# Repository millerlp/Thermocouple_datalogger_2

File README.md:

## Thermocouple_datalogger_2
### Luke Miller 2017

This repository contains code to run a 8-channel thermocouple
datalogger based on Arduino-type hardware. Currently there are 2 revisions,
A and B, which differ in the type of thermocouple-to-digital chip they use.
Revision A uses the older MAX31855K chip, while Revision B uses the more
recent MAX31856 that effectively superseded the MAX31855 series. Revision A
isn't recommended for new builds. 

The directory `TempTracker` contains the primary files used to run a 
datalogger board, while the `testing` directory contains various utilities
used to test the basic functions of a datalogger board or to help calibrate
a board. 

## Required libraries:
* https://github.com/millerlp/TClib2
* https://github.com/millerlp/Adafruit_MAX31856 - fork of the original Adafruit_MAX31856 library, mainly changed to return NAN temperature values automatically if there is an error. 
* https://github.com/millerlp/RTClib - to run the onboard real time clock chip DS3231M
* https://github.com/greiman/SdFat - for reading/writing SD cards
* https://github.com/greiman/SSD1306Ascii - for writing to OLED displays

## Hardware designs

Eagle `.sch` and `.brd` design files are provided in the `Eagle_files` directory, along
with images of the designs. 

## Parts list

See the file `Thermocouple_datalogger_parts.xlsx` in the `Parts` directory for a 
list of all of the chips and other parts needed to build a board. There are 
separate sheets for Revision A and B, be careful to use the appropriate sheet. The 
majority of the parts should be available from a single vendor such as Digikey.com,
but the OLED display screens and thermocouple connectors need to be sourced 
elsewhere. 

For the OLED displays, any 128x64 pixel I2C SSD1306-based board should 
work (typically 0.96" size). These are available from several vendors on sites like
Amazon or Ebay. Be aware that there are I2C and SPI versions available, but this 
datalogger board will only communicate via I2C, so buying the 4-pin I2C version of the
display is sensible.

The thermocouple "miniature" connectors will need to be sourced from a 
specialized vendor. The board is designed around Omega Engineering's PCC-SMP-V
connectors, which come in a minimum size batch of 5, so you'll need two batches to 
get 8. If you don't forsee needing to ever unplug a thermocouple, you could solder the
leads directly the board, forgoing the Omega connector. 

## Calibrating
The MAX3185x thermocouple chips are relatively accurate from the factory, and for
most purposes this will be sufficient, if you don't need absolute accuracy less than
1-2C. If you require sub-degree accurracy, calibration will be necessary, and this means
calibrating both the datalogger board and the individual thermocouple leads you use. 

Calibrating the datalogger board actually requires calibrating each of the 8 onboard 
MAX31856 chips separately, using a separate thermocouple calibrator such as the
Omega Engineering CL3515R. These devices are capable of outputting a millivolt signal
equivalent to what the relevant thermocouple type (K, T, J etc) would put out at a
specified temperature. The calibrator comes with a thermocouple cable that plugs 
directly into the thermocouple plugs on the datalogger board, mimicing a real 
thermocouple. The program `Calibration_routine_OLED_RevB` (or the RevA version) is meant
to be used with the external calibrator. After generating a set of calibration data for
a set of known temperatures, you can use the observed temperatures (recorded by the 
datalogger) and the known temperatures (from the calibrator) to fit a straight-line 
regression, and get the intercept (aka offset) and slope of the relationship between 
observed and expected readings. 

The program `Store_calibrations.ino` can then be used 
to upload the full set of 8 offset values and 8 slope values for the 8 MAX3185x 
chips to the datalogger's EEPROM onboard memory. The datalogger board will then have these
calibration values available to use every time it boots up. Typically I find that an 
individual MAX31855K or MAX31856 chip has a slope very near to 1.0 (ideal), but the 
intercept (aka offset) may often be +/- 0.5 to 1C off from ideal (0C offset). Therefore, calibration
is useful if you want the 8 individual channels on a board to be directly comparable to 
each other at the sub-degree level. The nominal temperature resolution of a MAX31855K chip is 0.25C (14-bit A-D converter) and the MAX31856 is 0.0078125 (19-bit A-D converter), but 
chip-to-chip variation from the factory can easily swamp that and only get you 
within +/- 2C of the true temperature in the normal biological range of temperatures. Careful calibration and housing the datalogger board in a thermally stable container 
should get you within 0.1C across channels. 

## Several words about the housing and thermal stability

The thermocouple-to-digital chips rely on an internal temperature sensor in the chip
itself to measure the "cold junction" temperature. This temperature is ideally equivalent
to the temperature at the point where the thermocouple plugs into the board and makes 
the transition from special thermocouple wire to the plain copper of the circuit board
(which is a thermocouple junction by definition). An accurate measurement of the 
distant ("hot") end of the thermocouple probe relies on the MAX3185x chip also knowing 
what the cold junction temperature is quite accurately. If the MAX3185x chip internal
temperature is a few degrees different than the thermocouple plug on the board, the
registered thermocouple temperature will also be off. Ideally, a block of material
that is thermally conductive (an "isothermal block") would be used to connect all 8 
of the MAX3185x chips and their respective thermocouple plugs, and thus keep all of 
those points at the same temperature. A bar of aluminum, copper, or brass, mounted so that 
it sits across the top of all the MAX3185x chips and also rests against the 
thermocouple plug terminals would be best, although these should not all be in 
electrical contact. To thermally couple the various parts without creating short 
circuits, adhesive thermal gap filler (often used to attach heat sinks to circuit 
boards and chips) can be used. This material is electrically non-conductive, but does
a reasonable job of allowing heat to transfer across it, and has the added benefit of
filling small gaps that might exist between an isothermal block and the various parts
due to height differences or variation in how flat the chips sit on the board. The RevB
board has two holes on the edges of the board positioned to help bolt an isothermal 
block across the tops of the MAX31856 chips. 

After provisioning an isothermal block, it would also be useful to then enclose the 
datalogger board in a housing that will stay relatively temperature-stable, or at 
least won't change temperature rapidly at different places. Surrounding the board in
insulating styrofoam may be desirable, and then placing that inside a plastic or metal housing that only exposes the front of the thermocouple connectors to the outside air. 
The RevB board is designed so that panel-mount buttons can be attached to wire leads and 
plugged into the board (via standard 0.1" headers), so that the buttons can be
mounted to a housing. The 2 OLED displays can be attached via 4-wire cables in the 
same manner. The rear/bottom edge of the board (opposite the thermocouple connectors) will 
need to be accessible through a housing wall so that the serial port, micro SD card slot, 
and 2.1mm DC power plug are accessible.

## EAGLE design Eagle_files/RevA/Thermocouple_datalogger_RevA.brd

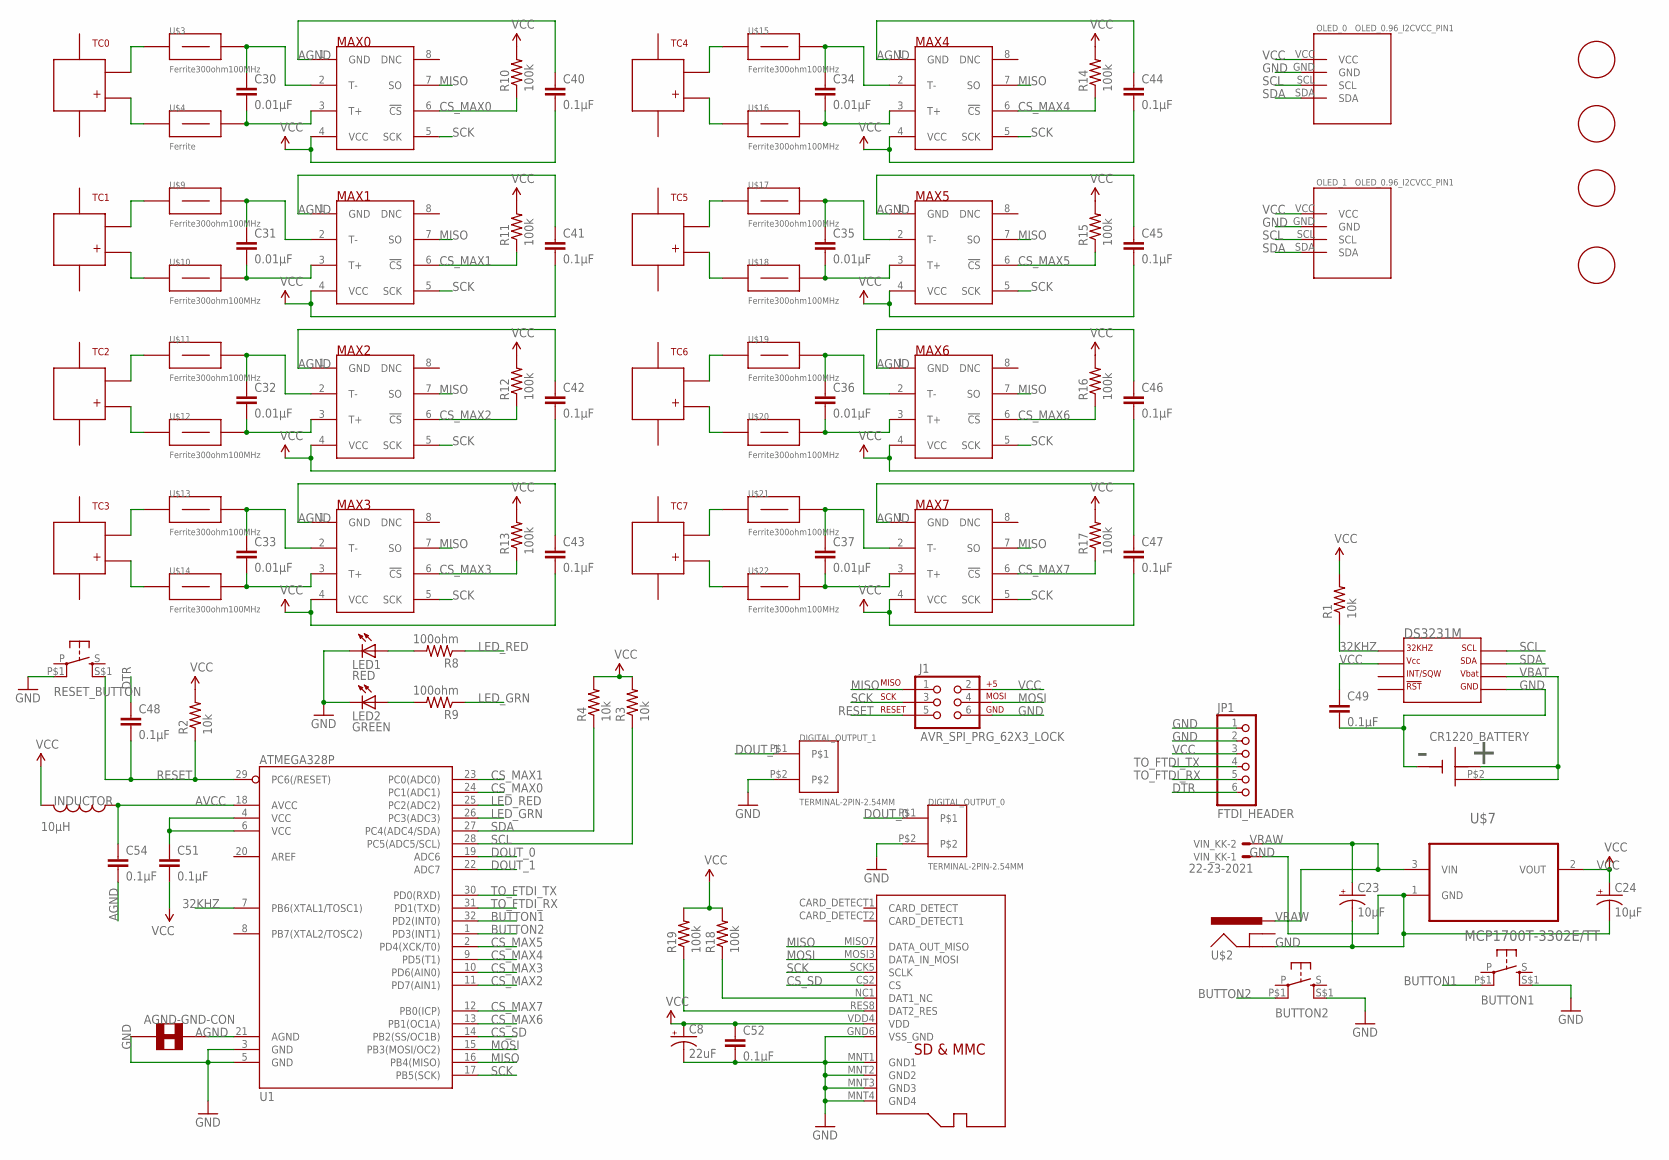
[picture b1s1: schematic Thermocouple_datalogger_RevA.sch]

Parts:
AGND-GND-CON: SOLDER_JUMPER_TRACESTANDARD; SJ_2S-TRACE
BUTTON1, BUTTON2: PUSHBUTTON_DPST_SMDSTANDARD; PUSHBUTTON_DPST_SMD
C8: 22uF; C0805_POL
C23, C24: 10µF; PANASONIC_B
C30, C31, C32, C33, C34, C35, C36, C37: 0.01µF; 0805
C40, C41, C42, C43, C44, C45, C46, C47, C48, C49, C51, C52, C54: 0.1µF; 0805
CR1220_BATTERY: CR1220_BATTERY_HOLDERSMD; CR1220_BATTERY_HOLDER_SMD
DIGITAL_OUTPUT_0, DIGITAL_OUTPUT_1: TERMINAL-2PIN-2.54MM
DS3231M: DS3231MSOIC-8; DS3231M_SOIC8
INDUCTOR: 10µH; I_0805
J1: AVR_SPI_PRG_62X3_LOCK; 2X3_LOCK
JP1: FTDI_HEADER; 1X06-BIGLOCK
LED1: RED; CHIPLED_0805
LED2: GREEN; CHIPLED_0805
MAX0, MAX1, MAX2, MAX3, MAX4, MAX5, MAX6, MAX7: MAX31855; SO08
OLED_0, OLED_1: OLED_0.96_I2CVCC_PIN1; OLED_0.96_I2C_VCC_PIN1
R1, R2, R3, R4: 10k; R0805
R8, R9: 100ohm; R0805
R10, R11, R12, R13, R14, R15, R16, R17, R18, R19: 100k; R0805
RESET_BUTTON: PUSHBUTTON_SMD; PUSHBUTTON_DPST_SMD
TC0, TC1, TC2, TC3, TC4, TC5, TC6, TC7: PCC-SMP-THERMOCOUPLEVERTICAL; PCC-SMP-V
U1: ATMEGA328P; TQFP32-08
U$2: JACK_2,1MM; POWER_JACK_DC_2,1MM
U$3, U$9, U$10, U$11, U$12, U$13, U$14, U$15, U$16, U$17, U$18, U$19, U$20, U$21, U$22: Ferrite300ohm100MHz; 0805
U$4: Ferrite; 0805
U$5: MICROSD_MOLEX_REVERSECURRENT; MICROSD_SOCKET_MOLEX_REVERSEMOUNT
U$6, U$23, U$24, U$25: HOLE-LAYOUT4-40-SOCKET-HEAD; 4-40-SCREW-HOLE
U$7: MCP1700T-3302E/TT; SOT95P237X112-3N
VIN_KK: 22-23-2021

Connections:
32KHZ: DS3231M.1 (P$1_32KHZ), R1.1, U1.7 (PB6(XTAL1/TOSC1))
AGND: AGND-GND-CON.2, C40.1, C41.1, C42.1, C43.1, C44.1, C45.1, C46.1, C47.1, C54.2, MAX0.1 (GND), MAX1.1 (GND), MAX2.1 (GND), MAX3.1 (GND), MAX4.1 (GND), MAX5.1 (GND), MAX6.1 (GND), MAX7.1 (GND), U1.21 (AGND)
AVCC: C54.1, INDUCTOR.P$1 (1), U1.18 (AVCC)
BUTTON1: BUTTON1.P$1 (P1), U1.32 (PD2(INT0))
BUTTON2: BUTTON2.P$1 (P1), U1.1 (PD3(INT1))
CS_MAX0: MAX0.6 (!CS), R10.1, U1.24 (PC1(ADC1))
CS_MAX1: MAX1.6 (!CS), R11.1, U1.23 (PC0(ADC0))
CS_MAX2: MAX2.6 (!CS), R12.1, U1.11 (PD7(AIN1))
CS_MAX3: MAX3.6 (!CS), R13.1, U1.10 (PD6(AIN0))
CS_MAX4: MAX4.6 (!CS), R14.1, U1.9 (PD5(T1))
CS_MAX5: MAX5.6 (!CS), R15.1, U1.2 (PD4(XCK/T0))
CS_MAX6: MAX6.6 (!CS), R16.1, U1.13 (PB1(OC1A))
CS_MAX7: MAX7.6 (!CS), R17.1, U1.12 (PB0(ICP))
CS_SD: U1.14 (PB2(SS/OC1B)), U$5.CS2 (CS)
DOUT_0: DIGITAL_OUTPUT_0.P$1, U1.19 (ADC6)
DOUT_1: DIGITAL_OUTPUT_1.P$1, U1.22 (ADC7)
DTR: C48.1, JP1.6
GND: AGND-GND-CON.1, BUTTON1.S$1 (S1), BUTTON2.S$1 (S1), C8.P$2_C (-), C23.-, C24.-, C49.2, C52.2, CR1220_BATTERY.GND, DIGITAL_OUTPUT_0.P$2, DIGITAL_OUTPUT_1.P$2, DS3231M.5 (P$5_GND), J1.6, JP1.1, JP1.2, LED1.C, LED2.C, OLED_0.GND, OLED_1.GND, RESET_BUTTON.P$1 (P1), U1.3 (GND), U1.5 (GND), U$2.P$2 (GND), U$5.GND6 (VSS_GND), U$5.MNT1 (GND1), U$5.MNT2 (GND2), U$5.MNT3 (GND3), U$5.MNT4 (GND4), U$7.1 (GND), VIN_KK.1
LED_GRN: R9.1, U1.26 (PC3(ADC3))
LED_RED: R8.1, U1.25 (PC2(ADC2))
MISO: J1.1, MAX0.7 (SO), MAX1.7 (SO), MAX2.7 (SO), MAX3.7 (SO), MAX4.7 (SO), MAX5.7 (SO), MAX6.7 (SO), MAX7.7 (SO), U1.16 (PB4(MISO)), U$5.MISO7 (DATA_OUT_MISO)
MOSI: J1.4, U1.15 (PB3(MOSI/OC2)), U$5.MOSI3 (DATA_IN_MOSI)
unnamed: C30.1, MAX0.2 (T-), U$3.2
unnamed: C30.2, MAX0.3 (T+), U$4.2
unnamed: TC0.P$2, U$4.1
unnamed: TC0.P$1, U$3.1
unnamed: LED1.A, R8.2
unnamed: R19.1, U$5.RES8 (DAT2_RES)
unnamed: R18.1, U$5.NC1 (DAT1_NC)
unnamed: C51.1, U1.4 (VCC), U1.6 (VCC)
unnamed: LED2.A, R9.2
unnamed: C31.1, MAX1.2 (T-), U$9.2
unnamed: C31.2, MAX1.3 (T+), U$10.2
unnamed: TC1.P$2, U$10.1
unnamed: TC1.P$1, U$9.1
unnamed: C32.1, MAX2.2 (T-), U$11.2
unnamed: C32.2, MAX2.3 (T+), U$12.2
unnamed: TC2.P$2, U$12.1
unnamed: TC2.P$1, U$11.1
unnamed: C33.1, MAX3.2 (T-), U$13.2
unnamed: C33.2, MAX3.3 (T+), U$14.2
unnamed: TC3.P$2, U$14.1
unnamed: TC3.P$1, U$13.1
unnamed: C34.1, MAX4.2 (T-), U$15.2
unnamed: C34.2, MAX4.3 (T+), U$16.2
unnamed: TC4.P$2, U$16.1
unnamed: TC4.P$1, U$15.1
unnamed: C35.1, MAX5.2 (T-), U$17.2
unnamed: C35.2, MAX5.3 (T+), U$18.2
unnamed: TC5.P$2, U$18.1
unnamed: TC5.P$1, U$17.1
unnamed: C36.1, MAX6.2 (T-), U$19.2
unnamed: C36.2, MAX6.3 (T+), U$20.2
unnamed: TC6.P$2, U$20.1
unnamed: TC6.P$1, U$19.1
unnamed: C37.1, MAX7.2 (T-), U$21.2
unnamed: C37.2, MAX7.3 (T+), U$22.2
unnamed: TC7.P$2, U$22.1
unnamed: TC7.P$1, U$21.1
RESET: C48.2, J1.5, R2.1, RESET_BUTTON.S$1 (S1), U1.29 (PC6(/RESET))
SCK: J1.3, MAX0.5 (SCK), MAX1.5 (SCK), MAX2.5 (SCK), MAX3.5 (SCK), MAX4.5 (SCK), MAX5.5 (SCK), MAX6.5 (SCK), MAX7.5 (SCK), U1.17 (PB5(SCK)), U$5.SCK5 (SCLK)
SCL: DS3231M.8 (P$8_SCL), OLED_0.SCL, OLED_1.SCL, R3.1, U1.28 (PC5(ADC5/SCL))
SDA: DS3231M.7 (P$7_SDA), OLED_0.SDA, OLED_1.SDA, R4.1, U1.27 (PC4(ADC4/SDA))
TO_FTDI_RX: JP1.5, U1.31 (PD1(TXD))
TO_FTDI_TX: JP1.4, U1.30 (PD0(RXD))
VBAT: CR1220_BATTERY.P$1 (VBAT), CR1220_BATTERY.P$2, DS3231M.6 (P$6_VBAT)
VCC: C8.P$1_A (+), C24.+, C40.2, C41.2, C42.2, C43.2, C44.2, C45.2, C46.2, C47.2, C49.1, C51.2, C52.1, DS3231M.2 (P$2_VCC), INDUCTOR.P$2 (2), J1.2, JP1.3, MAX0.4 (VCC), MAX1.4 (VCC), MAX2.4 (VCC), MAX3.4 (VCC), MAX4.4 (VCC), MAX5.4 (VCC), MAX6.4 (VCC), MAX7.4 (VCC), OLED_0.VCC, OLED_1.VCC, R1.2, R2.2, R3.2, R4.2, R10.2, R11.2, R12.2, R13.2, R14.2, R15.2, R16.2, R17.2, R18.2, R19.2, U$5.VDD4 (VDD), U$7.2 (VOUT)
VRAW: C23.+, U$2.P$1 (PWR), U$7.3 (VIN), VIN_KK.2

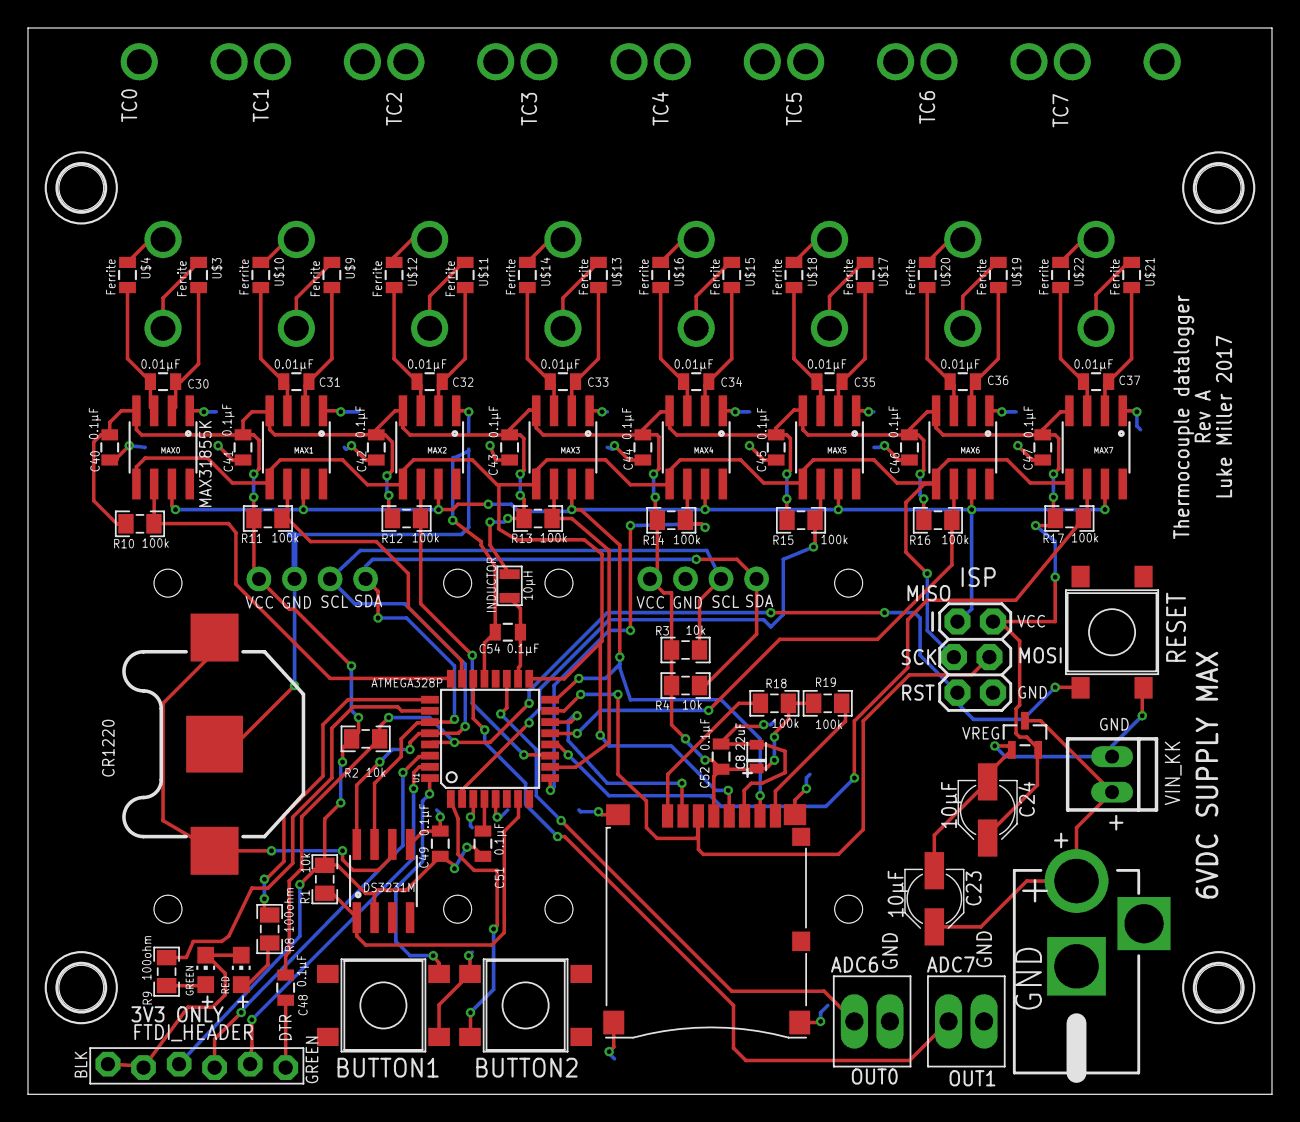
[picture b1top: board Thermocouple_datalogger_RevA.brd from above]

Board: 2 copper layers, 88.9 x 76.2 mm, 96 parts (1 on the bottom side), 68 nets.

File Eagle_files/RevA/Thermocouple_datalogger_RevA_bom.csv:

Thermocouple_datalogger_RevA 2017-06-01,,,,
Part,Value,Device,Package,Description
AGND-GND-CON,SOLDER_JUMPER_TRACESTANDARD,SOLDER_JUMPER_TRACESTANDARD,SJ_2S-TRACE,Solder jumper with trace
BUTTON1,,PUSHBUTTON_DPST_SMDSTANDARD,PUSHBUTTON_DPST_SMD,PUSHBUTTON DPST SMD
BUTTON2,,PUSHBUTTON_DPST_SMDSTANDARD,PUSHBUTTON_DPST_SMD,PUSHBUTTON DPST SMD
C8,22uF,CPOL-US0805,C0805_POL,"POLARIZED CAPACITOR, American symbol"
C23,10µF,CPOL-USB,PANASONIC_B,"POLARIZED CAPACITOR, American symbol"
C24,10µF,CPOL-USB,PANASONIC_B,"POLARIZED CAPACITOR, American symbol"
C30,0.01µF,CAP0805,805,Capacitor
C31,0.01µF,CAP0805,805,Capacitor
C32,0.01µF,CAP0805,805,Capacitor
C33,0.01µF,CAP0805,805,Capacitor
C34,0.01µF,CAP0805,805,Capacitor
C35,0.01µF,CAP0805,805,Capacitor
C36,0.01µF,CAP0805,805,Capacitor
C37,0.01µF,CAP0805,805,Capacitor
C40,0.1µF,CAP0805,805,Capacitor
C41,0.1µF,CAP0805,805,Capacitor
C42,0.1µF,CAP0805,805,Capacitor
C43,0.1µF,CAP0805,805,Capacitor
C44,0.1µF,CAP0805,805,Capacitor
C45,0.1µF,CAP0805,805,Capacitor
C46,0.1µF,CAP0805,805,Capacitor
C47,0.1µF,CAP0805,805,Capacitor
C48,0.1µF,CAP0805,805,Capacitor
C49,0.1µF,CAP0805,805,Capacitor
C51,0.1µF,CAP0805,805,Capacitor
C52,0.1µF,CAP0805,805,Capacitor
C54,0.1µF,CAP0805,805,Capacitor
CR1220_BATTERY,CR1220_BATTERY_HOLDERSMD,CR1220_BATTERY_HOLDERSMD,CR1220_BATTERY_HOLDER_SMD,CR1220 Battery Holder
DIGITAL_OUTPUT_0,TERMINAL-2PIN-2.54MM,TERMINAL-2PIN-2.54MM,TERMINAL-2PIN-2.54MM,"Terminal block 0.1 spacing"""
DIGITAL_OUTPUT_1,TERMINAL-2PIN-2.54MM,TERMINAL-2PIN-2.54MM,TERMINAL-2PIN-2.54MM,"Terminal block 0.1 spacing"""
DS3231M,DS3231MSOIC-8,DS3231MSOIC-8,DS3231M_SOIC8,DS3231M real time clock
INDUCTOR,10µH,INDUCTOR0805_TY,I_0805,Inductor
J1,AVR_SPI_PRG_62X3_LOCK,AVR_SPI_PRG_62X3_LOCK,2X3_LOCK,AVR ISP 6 Pin
JP1,FTDI_HEADER,PINHD-1X6LOCK,1X06-BIGLOCK,PIN HEADER
LED1,RED,LED0805,CHIPLED_0805,LEDs
LED2,GREEN,LED0805,CHIPLED_0805,LEDs
MAX0,MAX31855,MAX31855,SO08,"MAX31855 Thermocouple amplifier with cold junction compensation, SPI communication"
MAX1,MAX31855,MAX31855,SO08,"MAX31855 Thermocouple amplifier with cold junction compensation, SPI communication"
MAX2,MAX31855,MAX31855,SO08,"MAX31855 Thermocouple amplifier with cold junction compensation, SPI communication"
MAX3,MAX31855,MAX31855,SO08,"MAX31855 Thermocouple amplifier with cold junction compensation, SPI communication"
MAX4,MAX31855,MAX31855,SO08,"MAX31855 Thermocouple amplifier with cold junction compensation, SPI communication"
MAX5,MAX31855,MAX31855,SO08,"MAX31855 Thermocouple amplifier with cold junction compensation, SPI communication"
MAX6,MAX31855,MAX31855,SO08,"MAX31855 Thermocouple amplifier with cold junction compensation, SPI communication"
MAX7,MAX31855,MAX31855,SO08,"MAX31855 Thermocouple amplifier with cold junction compensation, SPI communication"
OLED_0,OLED_0.96_I2CVCC_PIN1,OLED_0.96_I2CVCC_PIN1,OLED_0.96_I2C_VCC_PIN1,CHECK VCC & GND PIN VARIANT
OLED_1,OLED_0.96_I2CVCC_PIN1,OLED_0.96_I2CVCC_PIN1,OLED_0.96_I2C_VCC_PIN1,CHECK VCC & GND PIN VARIANT
R1,10k,RESISTOR_SMDR0805,R0805,"RESISTOR, American symbol"
R2,10k,RESISTOR_SMDR0805,R0805,"RESISTOR, American symbol"
R3,10k,RESISTOR_SMDR0805,R0805,"RESISTOR, American symbol"
R4,10k,RESISTOR_SMDR0805,R0805,"RESISTOR, American symbol"
R8,100ohm,RESISTOR_SMDR0805,R0805,"RESISTOR, American symbol"
R9,100ohm,RESISTOR_SMDR0805,R0805,"RESISTOR, American symbol"
R10,100k,RESISTOR_SMDR0805,R0805,"RESISTOR, American symbol"
R11,100k,RESISTOR_SMDR0805,R0805,"RESISTOR, American symbol"
R12,100k,RESISTOR_SMDR0805,R0805,"RESISTOR, American symbol"
R13,100k,RESISTOR_SMDR0805,R0805,"RESISTOR, American symbol"
R14,100k,RESISTOR_SMDR0805,R0805,"RESISTOR, American symbol"
R15,100k,RESISTOR_SMDR0805,R0805,"RESISTOR, American symbol"
R16,100k,RESISTOR_SMDR0805,R0805,"RESISTOR, American symbol"
R17,100k,RESISTOR_SMDR0805,R0805,"RESISTOR, American symbol"
R18,100k,RESISTOR_SMDR0805,R0805,"RESISTOR, American symbol"
R19,100k,RESISTOR_SMDR0805,R0805,"RESISTOR, American symbol"
RESET_BUTTON,PUSHBUTTON_SMD,PUSHBUTTON_DPST_SMDSTANDARD,PUSHBUTTON_DPST_SMD,PUSHBUTTON DPST SMD
TC0,PCC-SMP-THERMOCOUPLEVERTICAL,PCC-SMP-THERMOCOUPLEVERTICAL,PCC-SMP-V,PCC-SMP
TC1,PCC-SMP-THERMOCOUPLEVERTICAL,PCC-SMP-THERMOCOUPLEVERTICAL,PCC-SMP-V,PCC-SMP
TC2,PCC-SMP-THERMOCOUPLEVERTICAL,PCC-SMP-THERMOCOUPLEVERTICAL,PCC-SMP-V,PCC-SMP
TC3,PCC-SMP-THERMOCOUPLEVERTICAL,PCC-SMP-THERMOCOUPLEVERTICAL,PCC-SMP-V,PCC-SMP
TC4,PCC-SMP-THERMOCOUPLEVERTICAL,PCC-SMP-THERMOCOUPLEVERTICAL,PCC-SMP-V,PCC-SMP
TC5,PCC-SMP-THERMOCOUPLEVERTICAL,PCC-SMP-THERMOCOUPLEVERTICAL,PCC-SMP-V,PCC-SMP
TC6,PCC-SMP-THERMOCOUPLEVERTICAL,PCC-SMP-THERMOCOUPLEVERTICAL,PCC-SMP-V,PCC-SMP
TC7,PCC-SMP-THERMOCOUPLEVERTICAL,PCC-SMP-THERMOCOUPLEVERTICAL,PCC-SMP-V,PCC-SMP
U$2,"JACK_2,1MM","POWER_JACK_2,1MM","POWER_JACK_DC_2,1MM","DC Power Jack, 2.1mm center pin."
U$3,Ferrite300ohm100MHz,FERRITE_BEAD0805,805,Ferrite bead
U$4,Ferrite300ohm100MHz,FERRITE_BEAD0805,805,Ferrite bead
U$5,MICROSD_MOLEX_REVERSECURRENT,MICROSD_MOLEX_REVERSECURRENT,MICROSD_SOCKET_MOLEX_REVERSEMOUNT,"Molex micro SD connector, push-push spring loaded, reverse"" mount"""
U$6,HOLE-LAYOUT4-40-SOCKET-HEAD,HOLE-LAYOUT4-40-SOCKET-HEAD,4-40-SCREW-HOLE,Drill hole
U$7,MCP1700T-3302E/TT,MCP1700T-3302E/TT,SOT95P237X112-3N,Low Quiescent Current LDO
U$9,Ferrite300ohm100MHz,FERRITE_BEAD0805,805,Ferrite bead
U$10,Ferrite300ohm100MHz,FERRITE_BEAD0805,805,Ferrite bead
U$11,Ferrite300ohm100MHz,FERRITE_BEAD0805,805,Ferrite bead
U$12,Ferrite300ohm100MHz,FERRITE_BEAD0805,805,Ferrite bead
U$13,Ferrite300ohm100MHz,FERRITE_BEAD0805,805,Ferrite bead
U$14,Ferrite300ohm100MHz,FERRITE_BEAD0805,805,Ferrite bead
U$15,Ferrite300ohm100MHz,FERRITE_BEAD0805,805,Ferrite bead
U$16,Ferrite300ohm100MHz,FERRITE_BEAD0805,805,Ferrite bead
U$17,Ferrite300ohm100MHz,FERRITE_BEAD0805,805,Ferrite bead
U$18,Ferrite300ohm100MHz,FERRITE_BEAD0805,805,Ferrite bead
U$19,Ferrite300ohm100MHz,FERRITE_BEAD0805,805,Ferrite bead
U$20,Ferrite300ohm100MHz,FERRITE_BEAD0805,805,Ferrite bead
U$21,Ferrite300ohm100MHz,FERRITE_BEAD0805,805,Ferrite bead
U$22,Ferrite300ohm100MHz,FERRITE_BEAD0805,805,Ferrite bead
U$23,HOLE-LAYOUT4-40-SOCKET-HEAD,HOLE-LAYOUT4-40-SOCKET-HEAD,4-40-SCREW-HOLE,Drill hole
U$24,HOLE-LAYOUT4-40-SOCKET-HEAD,HOLE-LAYOUT4-40-SOCKET-HEAD,4-40-SCREW-HOLE,Drill hole
U$25,HOLE-LAYOUT4-40-SOCKET-HEAD,HOLE-LAYOUT4-40-SOCKET-HEAD,4-40-SCREW-HOLE,Drill hole
U1,ATMEGA328P,ATMEGA328_SMT,TQFP32-08,32-Pin Atmega328
VIN_KK,22-23-2021,22-23-2021,22-23-2021,Molex KK series

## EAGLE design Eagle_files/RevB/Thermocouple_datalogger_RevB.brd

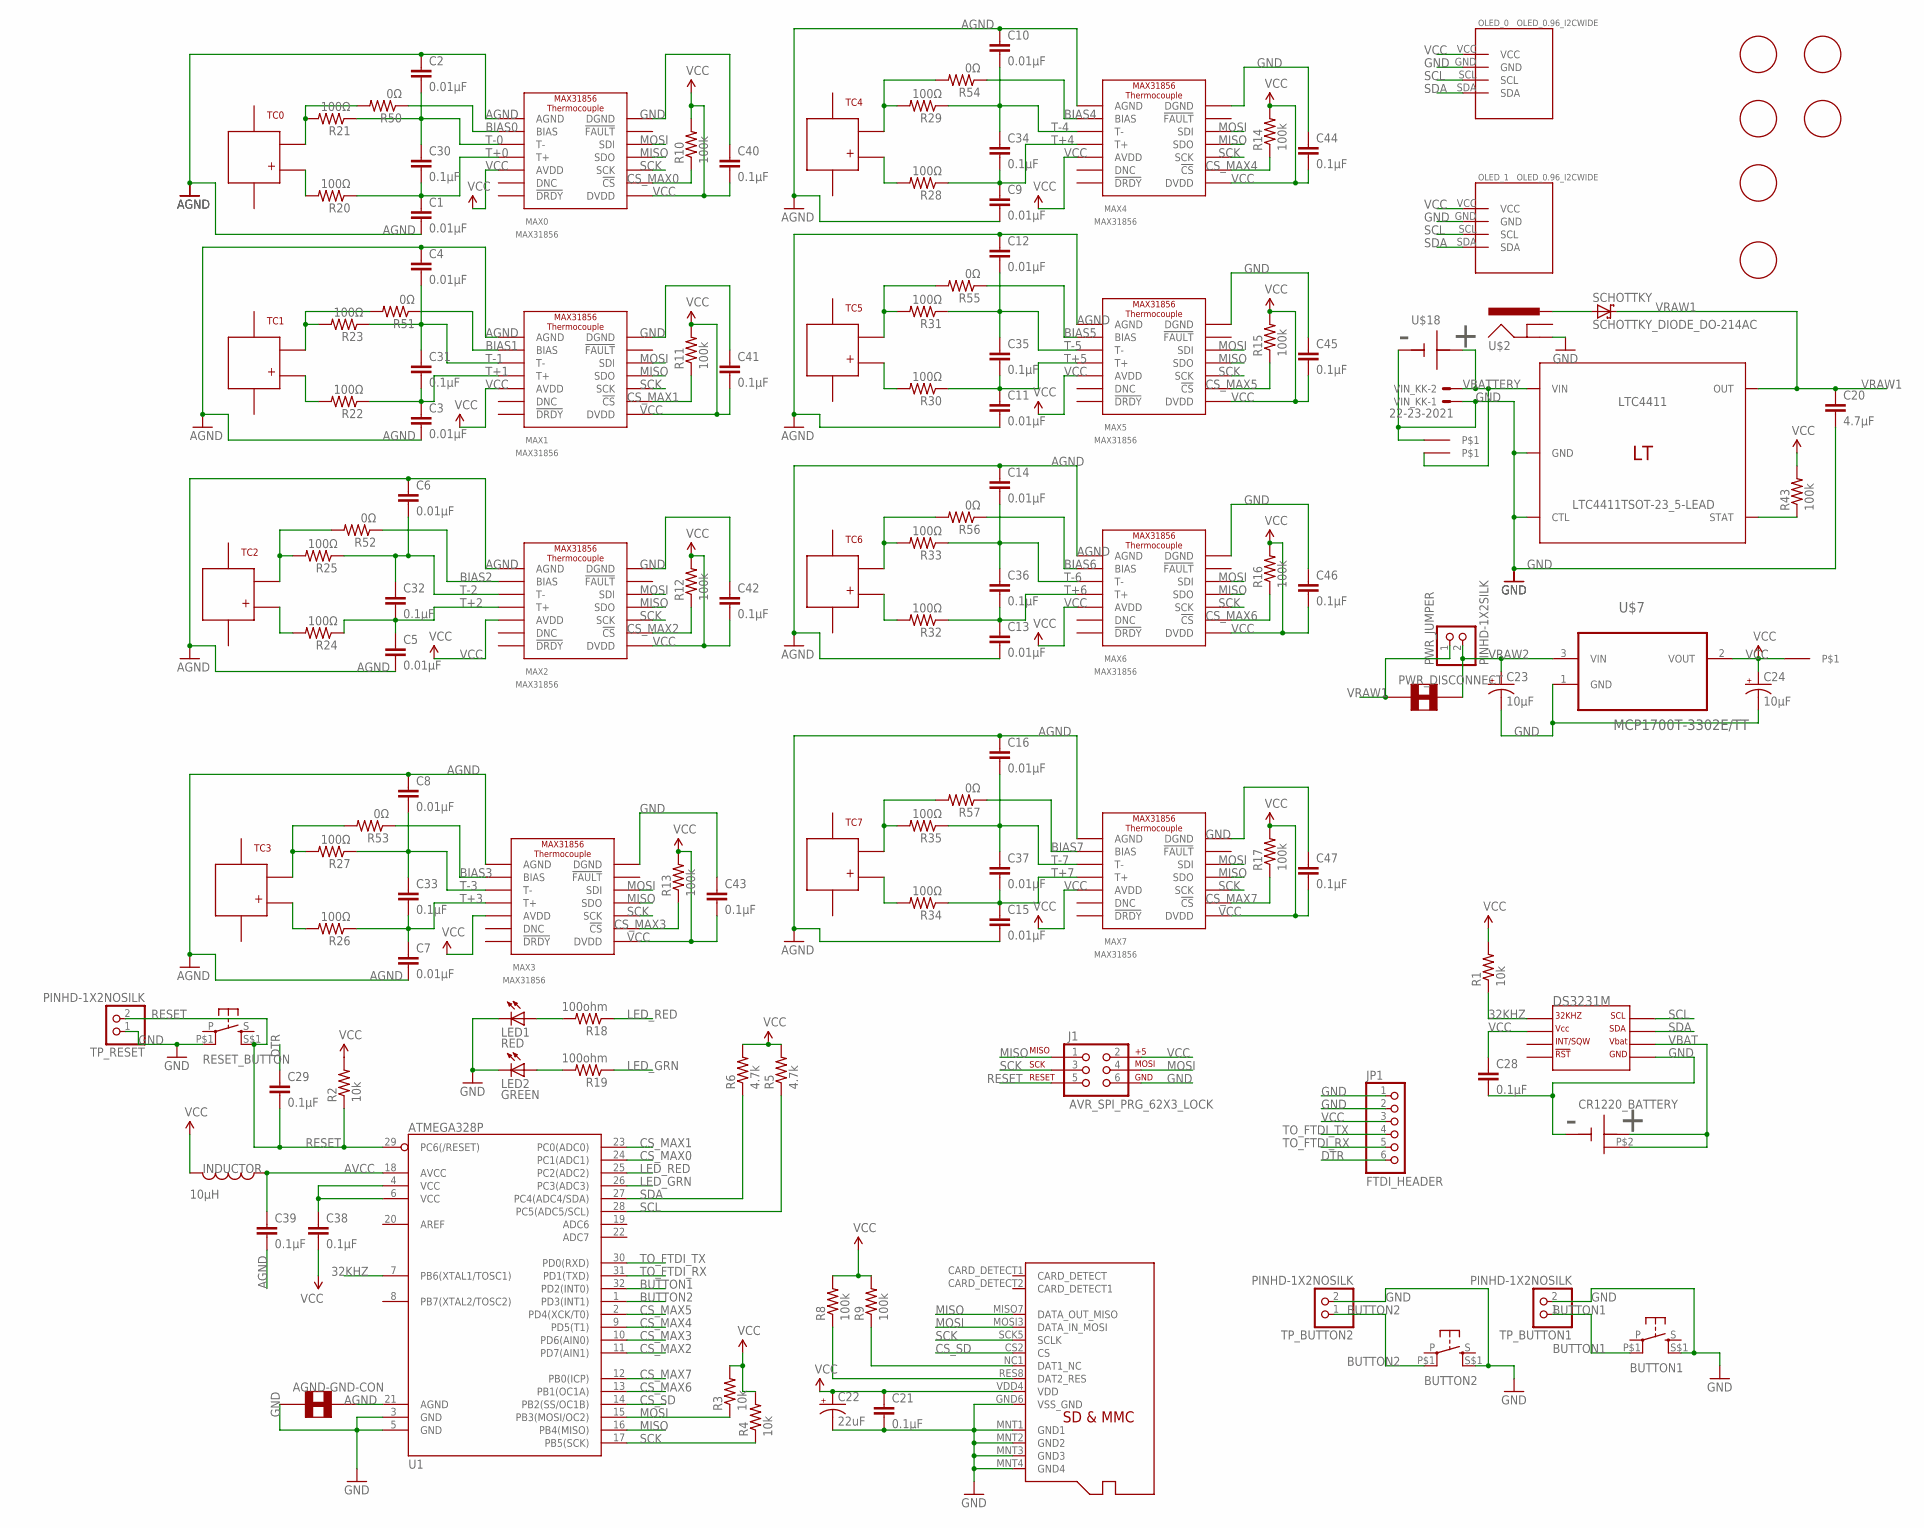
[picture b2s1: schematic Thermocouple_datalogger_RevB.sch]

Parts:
AGND-GND-CON: SOLDER_JUMPER_TRACESTANDARD; SJ_2S-TRACE
BUTTON1, BUTTON2: PUSHBUTTON_DPST_SMDSTANDARD; PUSHBUTTON_DPST_SMD
C1, C2, C3, C4, C5, C6, C7, C8, C9, C10, C11, C12, C13, C14, C15, C16, C37: 0.01µF; 0805
C20: 4.7µF; 0805
C21, C28, C29, C30, C31, C32, C33, C34, C35, C36, C38, C39, C40, C41, C42, C43, C44, C45, C46, C47: 0.1µF; 0805
C22: 22uF; C0805_POL
C23, C24: 10µF; PANASONIC_B
CR1220_BATTERY: CR1220_BATTERY_HOLDERSMD; CR1220_BATTERY_HOLDER_SMD
DS3231M: DS3231MSOIC-8; DS3231M_SOIC8
INDUCTOR: 10µH; I_0805
J1: AVR_SPI_PRG_62X3_LOCK; 2X3_LOCK
JP1: FTDI_HEADER; 1X06-RIGHT_ANGLE
LED1: RED; CHIPLED_0805
LED2: GREEN; CHIPLED_0805
LTC4411: LTC4411TSOT-23_5-LEAD; TSOT-23_5-LEAD
MAX0, MAX1, MAX2, MAX3, MAX4, MAX5, MAX6, MAX7: MAX31856; MAX31856_TSSOP14
OLED_0, OLED_1: OLED_0.96_I2CWIDE; OLED_0.96_I2C_VCC_PIN1_WIDE
PWR_DISCONNECT: SOLDER_JUMPER_TRACESTANDARD; SJ_2S-TRACE
PWR_JUMPER: PINHD-1X2SILK; 1X02
R1, R2, R3, R4: 10k; R0805
R5, R6: 4.7k; R0805
R8, R9, R10, R11, R12, R13, R14, R15, R16, R17, R43: 100k; R0805
R18, R19: 100ohm; R0805
R20, R21, R22, R23, R24, R25, R26, R27, R28, R29, R30, R31, R32, R33, R34, R35: 100Ω; R0805
R50, R51, R52, R53, R54, R55, R56, R57: 0Ω; R0805
RESET_BUTTON: PUSHBUTTON_SMD; PUSHBUTTON_DPST_SMD
SCHOTTKY: SCHOTTKY_DIODE_DO-214AC; DO214AC
TC0, TC1, TC2, TC3, TC4, TC5, TC6, TC7: PCC-SMP-THERMOCOUPLEVERTICAL; PCC-SMP-V
TP_BUTTON1, TP_BUTTON2: PINHD-1X2NOSILK; 1X02_NOSILK
TP_GND: PINHD-1X1STANDARD; 1X01
TP_RESET: PINHD-1X2NOSILK; 1X02_NOSILK
TP_VBAT: PINHD-1X1STANDARD; 1X01
U1: ATMEGA328P; TQFP32-08
U$2: JACK_2,1MM; POWER_JACK_DC_2,1MM
U$5: MICROSD_MOLEX_REVERSECURRENT; MICROSD_SOCKET_MOLEX_REVERSEMOUNT
U$6, U$15, U$16, U$23, U$24, U$25: HOLE-LAYOUT4-40-SOCKET-HEAD; 4-40-SCREW-HOLE
U$7: MCP1700T-3302E/TT; SOT95P237X112-3N
U$18: BATTERY_4XAA; BATTERY_4XAA_PTH
VCC: PINHD-1X1STANDARD; 1X01
VIN_KK: 22-23-2021

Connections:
32KHZ: DS3231M.1 (P$1_32KHZ), R1.1, U1.7 (PB6(XTAL1/TOSC1))
AGND: AGND-GND-CON.2, C1.2, C2.1, C3.2, C4.1, C5.2, C6.1, C7.2, C8.1, C9.2, C10.1, C11.2, C12.1, C13.2, C14.1, C15.2, C16.1, C39.2, MAX0.AGND, MAX1.AGND, MAX2.AGND, MAX3.AGND, MAX4.AGND, MAX5.AGND, MAX6.AGND, MAX7.AGND, U1.21 (AGND)
AVCC: C39.1, INDUCTOR.P$1 (1), U1.18 (AVCC)
BIAS0: MAX0.BIAS, R50.1
BIAS1: MAX1.BIAS, R51.1
BIAS2: MAX2.BIAS, R52.1
BIAS3: MAX3.BIAS, R53.1
BIAS4: MAX4.BIAS, R54.1
BIAS5: MAX5.BIAS, R55.1
BIAS6: MAX6.BIAS, R56.1
BIAS7: MAX7.BIAS, R57.1
BUTTON1: BUTTON1.P$1 (P1), TP_BUTTON1.1, U1.32 (PD2(INT0))
BUTTON2: BUTTON2.P$1 (P1), TP_BUTTON2.1, U1.1 (PD3(INT1))
CS_MAX0: MAX0.!CS, R10.1, U1.24 (PC1(ADC1))
CS_MAX1: MAX1.!CS, R11.1, U1.23 (PC0(ADC0))
CS_MAX2: MAX2.!CS, R12.1, U1.11 (PD7(AIN1))
CS_MAX3: MAX3.!CS, R13.1, U1.10 (PD6(AIN0))
CS_MAX4: MAX4.!CS, R14.1, U1.9 (PD5(T1))
CS_MAX5: MAX5.!CS, R15.1, U1.2 (PD4(XCK/T0))
CS_MAX6: MAX6.!CS, R16.1, U1.13 (PB1(OC1A))
CS_MAX7: MAX7.!CS, R17.1, U1.12 (PB0(ICP))
CS_SD: U1.14 (PB2(SS/OC1B)), U$5.CS2 (CS)
DTR: C29.1, JP1.6
GND: AGND-GND-CON.1, BUTTON1.S$1 (S1), BUTTON2.S$1 (S1), C20.2, C21.2, C22.P$2_C (-), C23.-, C24.-, C28.2, C40.1, C41.1, C42.1, C43.1, C44.1, C45.1, C46.1, C47.1, CR1220_BATTERY.GND, DS3231M.5 (P$5_GND), J1.6, JP1.1, JP1.2, LED1.C, LED2.C, LTC4411.2 (GND), LTC4411.3 (CTL), MAX0.DGND, MAX1.DGND, MAX2.DGND, MAX3.DGND, MAX4.DGND, MAX5.DGND, MAX6.DGND, MAX7.DGND, OLED_0.GND, OLED_1.GND, RESET_BUTTON.P$1 (P1), TP_BUTTON1.2, TP_BUTTON2.2, TP_GND.1, TP_RESET.1, U1.3 (GND), U1.5 (GND), U$2.P$2 (GND), U$5.GND6 (VSS_GND), U$5.MNT1 (GND1), U$5.MNT2 (GND2), U$5.MNT3 (GND3), U$5.MNT4 (GND4), U$7.1 (GND), U$18.GND, VIN_KK.1
LED_GRN: R19.1, U1.26 (PC3(ADC3))
LED_RED: R18.1, U1.25 (PC2(ADC2))
MISO: J1.1, MAX0.SDO, MAX1.SDO, MAX2.SDO, MAX3.SDO, MAX4.SDO, MAX5.SDO, MAX6.SDO, MAX7.SDO, U1.16 (PB4(MISO)), U$5.MISO7 (DATA_OUT_MISO)
MOSI: J1.4, MAX0.SDI, MAX1.SDI, MAX2.SDI, MAX3.SDI, MAX4.SDI, MAX5.SDI, MAX6.SDI, MAX7.SDI, R3.1, U1.15 (PB3(MOSI/OC2)), U$5.MOSI3 (DATA_IN_MOSI)
unnamed: LTC4411.4 (STAT), R43.1
unnamed: SCHOTTKY.A, U$2.P$1 (PWR)
unnamed: LED1.A, R18.2
unnamed: R8.1, U$5.RES8 (DAT2_RES)
unnamed: R9.1, U$5.NC1 (DAT1_NC)
unnamed: C38.1, U1.4 (VCC), U1.6 (VCC)
unnamed: LED2.A, R19.2
unnamed: R22.2, TC1.P$2
unnamed: R23.2, R51.2, TC1.P$1
unnamed: R24.2, TC2.P$2
unnamed: R25.2, R52.2, TC2.P$1
unnamed: R26.2, TC3.P$2
unnamed: R27.2, R53.2, TC3.P$1
unnamed: R28.2, TC4.P$2
unnamed: R29.2, R54.2, TC4.P$1
unnamed: R30.2, TC5.P$2
unnamed: R31.2, R55.2, TC5.P$1
unnamed: R32.2, TC6.P$2
unnamed: R33.2, R56.2, TC6.P$1
unnamed: R34.2, TC7.P$2
unnamed: R35.2, R57.2, TC7.P$1
RESET: C29.2, J1.5, R2.1, RESET_BUTTON.S$1 (S1), TP_RESET.2, U1.29 (PC6(/RESET))
SCK: J1.3, MAX0.SCK, MAX1.SCK, MAX2.SCK, MAX3.SCK, MAX4.SCK, MAX5.SCK, MAX6.SCK, MAX7.SCK, R4.1, U1.17 (PB5(SCK)), U$5.SCK5 (SCLK)
SCL: DS3231M.8 (P$8_SCL), OLED_0.SCL, OLED_1.SCL, R5.1, U1.28 (PC5(ADC5/SCL))
SDA: DS3231M.7 (P$7_SDA), OLED_0.SDA, OLED_1.SDA, R6.1, U1.27 (PC4(ADC4/SDA))
T+0: C1.1, C30.2, MAX0.T+, R20.1
T+0_TERM: R20.2, TC0.P$2
T+1: C3.1, C31.2, MAX1.T+, R22.1
T+2: C5.1, C32.2, MAX2.T+, R24.1
T+3: C7.1, C33.2, MAX3.T+, R26.1
T+4: C9.1, C34.2, MAX4.T+, R28.1
T+5: C11.1, C35.2, MAX5.T+, R30.1
T+6: C13.1, C36.2, MAX6.T+, R32.1
T+7: C15.1, C37.2, MAX7.T+, R34.1
T-0: C2.2, C30.1, MAX0.T-, R21.1
T-0_TERM: R21.2, R50.2, TC0.P$1
T-1: C4.2, C31.1, MAX1.T-, R23.1
T-2: C6.2, C32.1, MAX2.T-, R25.1
T-3: C8.2, C33.1, MAX3.T-, R27.1
T-4: C10.2, C34.1, MAX4.T-, R29.1
T-5: C12.2, C35.1, MAX5.T-, R31.1
T-6: C14.2, C36.1, MAX6.T-, R33.1
T-7: C16.2, C37.1, MAX7.T-, R35.1
TO_FTDI_RX: JP1.5, U1.31 (PD1(TXD))
TO_FTDI_TX: JP1.4, U1.30 (PD0(RXD))
VBAT: CR1220_BATTERY.P$1 (VBAT), CR1220_BATTERY.P$2, DS3231M.6 (P$6_VBAT)
VBATTERY: LTC4411.1 (VIN), TP_VBAT.1, U$18.VBAT, VIN_KK.2
VCC: C21.1, C22.P$1_A (+), C24.+, C28.1, C38.2, C40.2, C41.2, C42.2, C43.2, C44.2, C45.2, C46.2, C47.2, DS3231M.2 (P$2_VCC), INDUCTOR.P$2 (2), J1.2, JP1.3, MAX0.AVDD, MAX0.DVDD, MAX1.AVDD, MAX1.DVDD, MAX2.AVDD, MAX2.DVDD, MAX3.AVDD, MAX3.DVDD, MAX4.AVDD, MAX4.DVDD, MAX5.AVDD, MAX5.DVDD, MAX6.AVDD, MAX6.DVDD, MAX7.AVDD, MAX7.DVDD, OLED_0.VCC, OLED_1.VCC, R1.2, R2.2, R3.2, R4.2, R5.2, R6.2, R8.2, R9.2, R10.2, R11.2, R12.2, R13.2, R14.2, R15.2, R16.2, R17.2, R43.2, U$5.VDD4 (VDD), U$7.2 (VOUT), VCC.1
VRAW1: C20.1, LTC4411.5 (OUT), PWR_DISCONNECT.1, PWR_JUMPER.1, SCHOTTKY.C
VRAW2: C23.+, PWR_DISCONNECT.2, PWR_JUMPER.2, U$7.3 (VIN)
